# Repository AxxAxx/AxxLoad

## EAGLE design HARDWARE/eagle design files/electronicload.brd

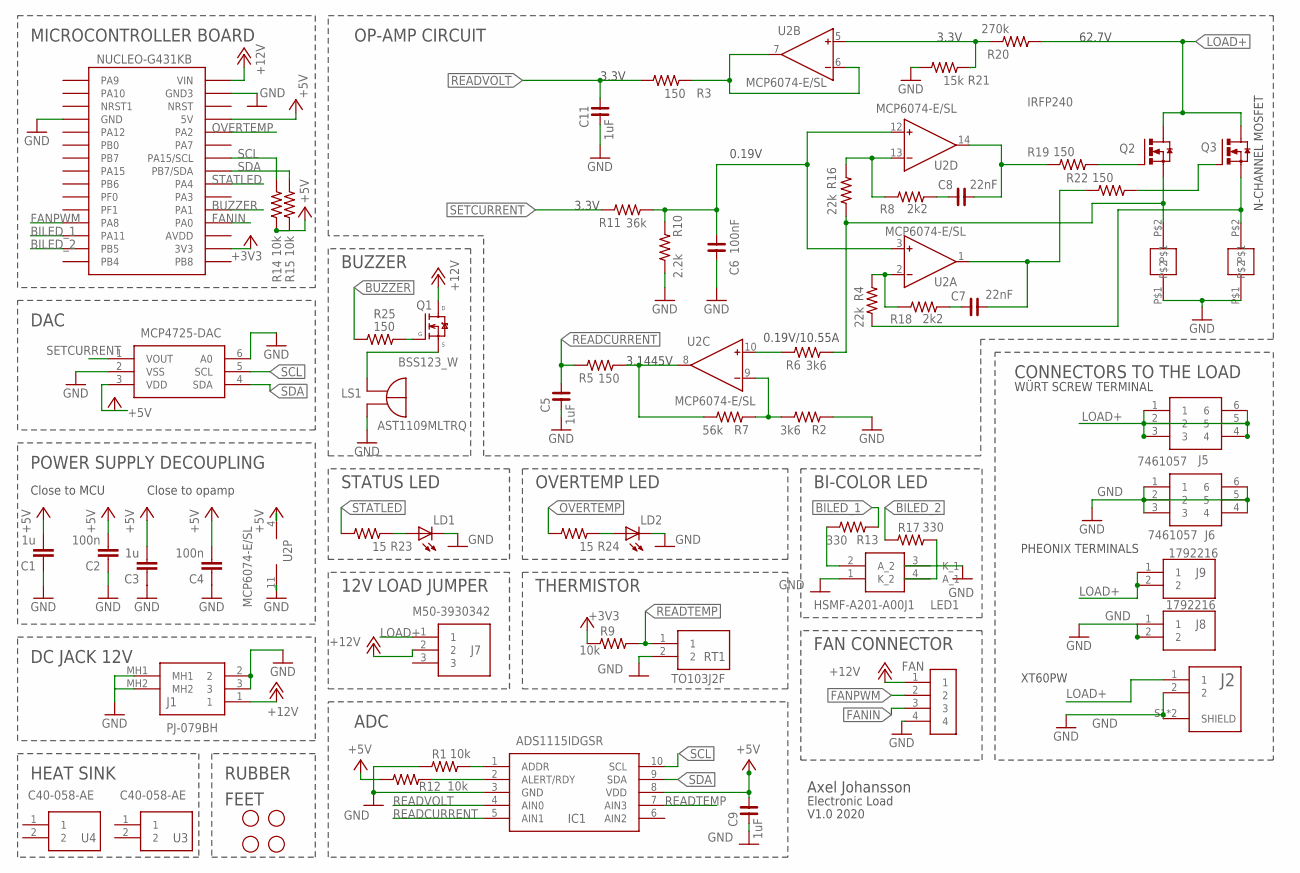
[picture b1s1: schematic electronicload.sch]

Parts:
C1, C3: 1u; C0603K; TOLERANCE 10%; VOLTAGE 16V; DIGIKEY 311-1444-1-ND
C2, C4: 100n; C0603K; TOLERANCE 10%; VOLTAGE 50V; DIGIKEY 445-7456-1-ND
C5, C9, C11: 1uF; C0805
C6: 100nF; C0805
C7, C8: 22nF; C0805
FAN: B4B-PH-K-S(LF)(SN); JST_B4B-PH-K-S(LF)(SN)
IC1: ADS1115IDGSR; SOP50P490X110-10N
J1: PJ-079BH; PJ079BH
J2: XT60PW-F; AMASS_XT60PW-F
J5, J6: 7461057
J7: M50-3930342; M503930342
J8, J9: 1792216
LD1, LD2: LEDCHIP-LED0805; CHIP-LED0805
LED1: HSMF-A201-A00J1; AVAGO_PLCC4
LS1: AST1109MLTRQ; XDCR_AST1109MLTRQ
MCP4725-DAC: MCP4725A0T-E_CH; SOT95P270X145-6N
Q1: BSS123_W; SOT23_GSD_W
Q2, Q3: IRFP240; TO247AC
R1, R9, R12, R14, R15: 10k; R0805
R2, R6: 3k6; R0805
R3, R5, R19, R22, R25: 150; R0805
R4, R16: 22k; R0805
R7: 56k; R0805
R8, R18: 2k2; R0805
R10: 2.2k; R0805
R11: 36k; R0805
R13, R17: 330; R0805
R20: 270k; R0805
R21: 15k; R0805
R23, R24: 15; R0805
RT1: TO103J2F; TO508P483X1016X2337-2P
U2: MCP6074-E/SL; SO14
U3, U4: C40-058-AE; C40058AE
U$1: NANO
U$2, U$5, U$6, U$7: RUBBER_FEET
U$3, U$4: CURRENTSENSE_RESISTOR_SMD2817

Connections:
+3V3: R9.1, U$1.RX1 (3V3)
+5V: C1.2, C2.2, C3.2, C4.2, C9.2, IC1.8 (VDD), MCP4725-DAC.3 (VDD), R12.1, R14.1, R15.1, U2.4 (V+), U$1.D9 (5V)
+12V: FAN.1, J1.1, J7.2, Q1.D, U$1.D12 (VIN)
BILED_1: R13.1, U$1.RST (PA11)
BILED_2: R17.1, U$1.GND (PB5)
BUZZER: R25.1, U$1.D2 (PA1)
FANIN: FAN.3, U$1.GND1 (PA0)
FANPWM: FAN.2, U$1.5V (PA8)
GND: C1.1, C2.1, C3.1, C4.1, C5.1, C6.1, C9.1, C11.1, FAN.4, IC1.3 (GND), J1.2, J1.3, J1.MH1, J1.MH2, J2.2, J2.S1 (SHIELD), J2.S2 (SHIELD), J6.1, J6.2, J6.3, J6.4, J6.5, J6.6, J8.1, J8.2, LD1.C, LD2.C, LED1.1 (K_2), LED1.3 (K_1), LS1.2, MCP4725-DAC.2 (VSS), MCP4725-DAC.6 (A0), R1.1, R2.1, R10.2, R21.2, RT1.2, U2.11 (V-), U$1.A0 (GND), U$1.D11 (GND3), U$3.P$1, U$4.P$1
LOAD+: J2.1, J5.1, J5.2, J5.3, J5.4, J5.5, J5.6, J7.1, J9.1, J9.2, Q2.2 (D), Q3.2 (D), R20.1
unnamed: C8.1, R19.1, U2.14 (OUT)
unnamed: R3.1, U2.6 (IN-), U2.7 (OUT)
unnamed: R6.2, U2.10 (IN+)
unnamed: R8.1, R16.1, U2.13 (IN-)
unnamed: R20.2, R21.1, U2.5 (IN+)
unnamed: Q2.1 (G), R19.2
unnamed: R2.2, R7.1, U2.9 (IN-)
unnamed: IC1.1 (ADDR), R1.2
unnamed: R5.1, R7.2, U2.8 (OUT)
unnamed: IC1.2 (ALERT/RDY), R12.2
unnamed: LED1.4 (A_1), R17.2
unnamed: C8.2, R8.2
unnamed: LED1.2 (A_2), R13.2
unnamed: Q2.3 (S), R6.1, R16.2, U$4.P$2
unnamed: Q3.3 (S), R4.2, U$3.P$2
unnamed: R4.1, R18.1, U2.2 (IN-)
unnamed: C6.2, R10.1, R11.1, U2.3 (IN+), U2.12 (IN+)
unnamed: C7.2, R18.2
unnamed: Q3.1 (G), R22.2
unnamed: C7.1, R22.1, U2.1 (OUT)
unnamed: LD1.A, R23.1
unnamed: LD2.A, R24.1
unnamed: LS1.1, Q1.S
unnamed: Q1.G, R25.2
OVERTEMP: R24.2, U$1.D8 (PA2)
READCURRENT: C5.2, IC1.5 (AIN1), R5.2
READTEMP: IC1.7 (AIN3), R9.2, RT1.1
READVOLT: C11.2, IC1.4 (AIN0), R3.2
SCL: IC1.10 (SCL), MCP4725-DAC.5 (SCL), R14.2, U$1.D6 (PA15/SCL)
SDA: IC1.9 (SDA), MCP4725-DAC.4 (SDA), R15.2, U$1.D5 (PB7/SDA)
SETCURRENT: MCP4725-DAC.1 (VOUT), R11.2
STATLED: R23.2, U$1.D4 (PA4)

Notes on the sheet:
POWER SUPPLY DECOUPLING
PHEONIX TERMINALS
WÜRT SCREW TERMINAL
N-CHANNEL MOSFET
3.3V
62.7V
0.19V
0.19V/10.55A
3.1445V
Electronic Load
V1.0 2020
Close to MCU
Close to opamp
HEAT SINK
CONNECTORS TO THE LOAD
MICROCONTROLLER BOARD
OP-AMP CIRCUIT
Axel Johansson
DAC
RUBBER
FEET
DC JACK 12V
THERMISTOR
ADC
FAN CONNECTOR
XT60PW
BI-COLOR LED
12V LOAD JUMPER
STATUS LED
OVERTEMP LED
BUZZER

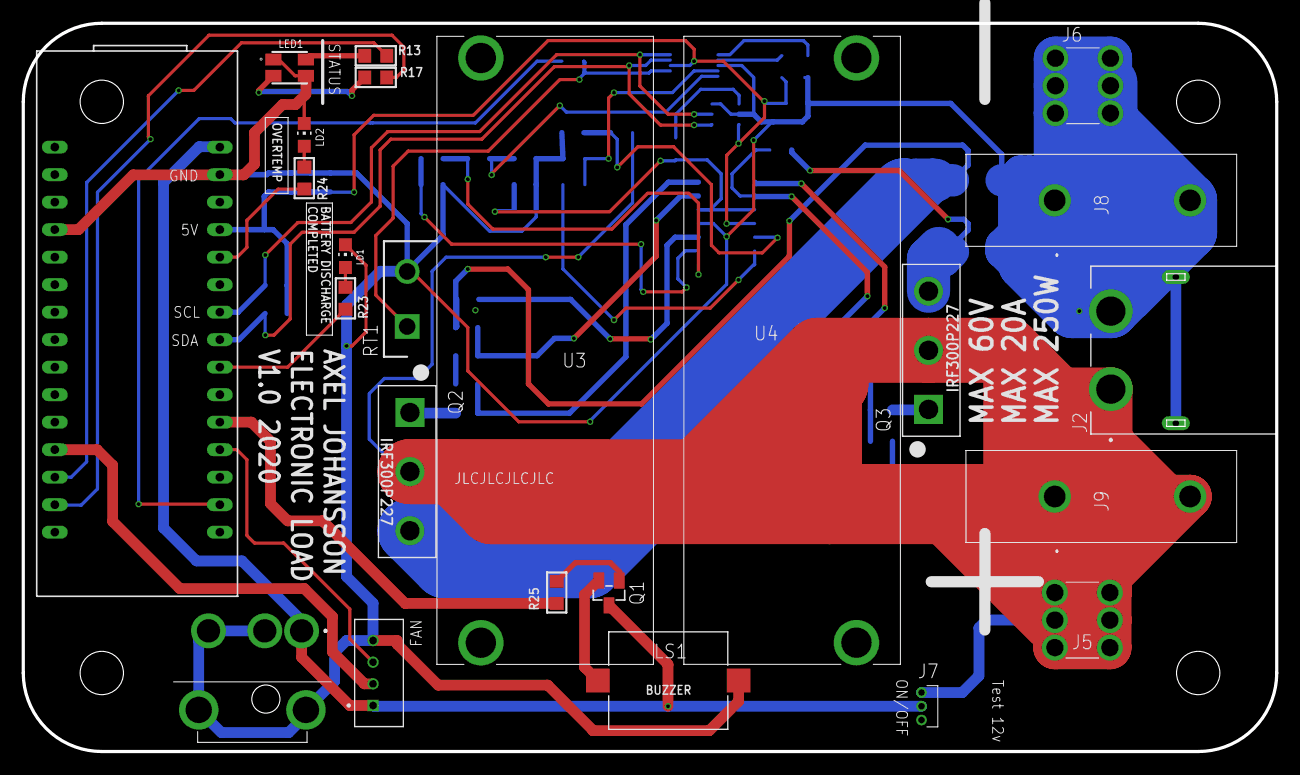
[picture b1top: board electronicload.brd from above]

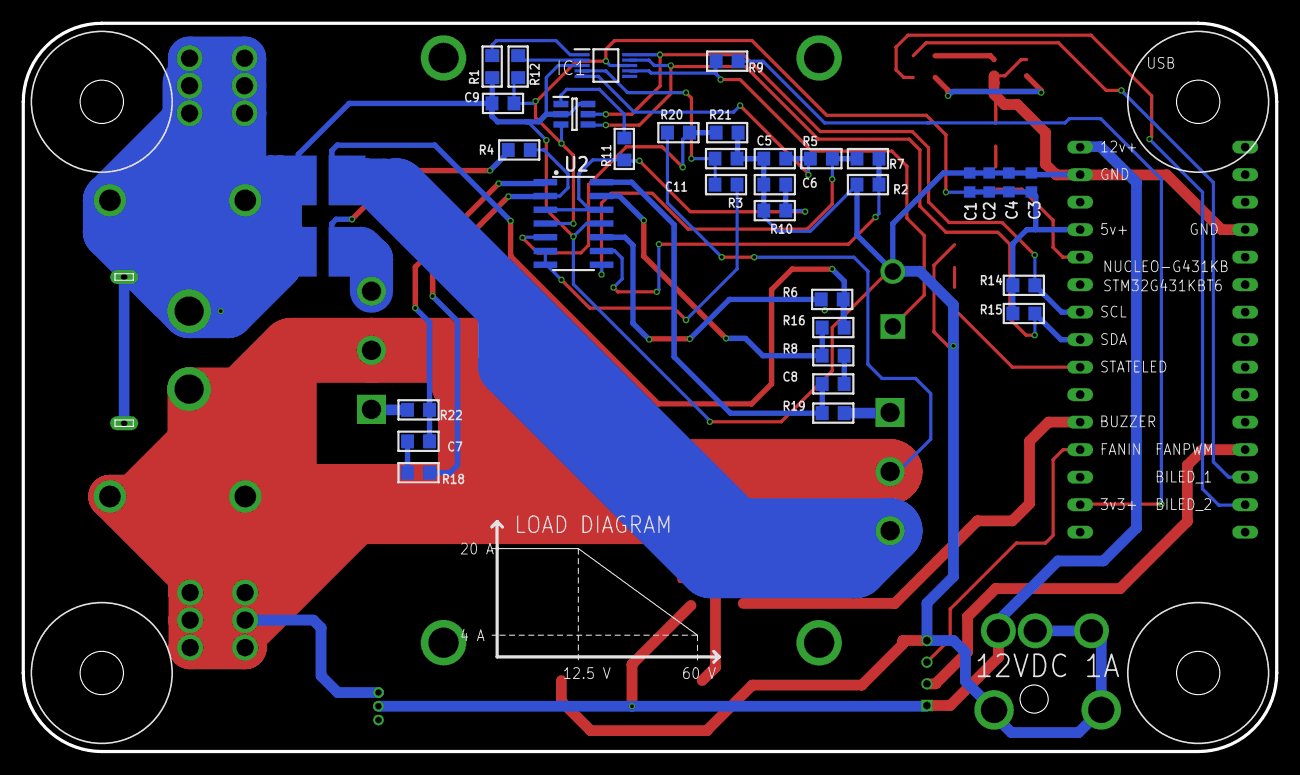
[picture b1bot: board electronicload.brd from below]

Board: 2 copper layers, 115.8 x 67.2 mm, 63 parts (35 on the bottom side), 42 nets.

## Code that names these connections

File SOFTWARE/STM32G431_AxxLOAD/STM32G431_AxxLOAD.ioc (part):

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Mcu.Name=STM32G431K(6-8-B)Tx
Mcu.Package=LQFP32
Mcu.UserName=STM32G431KBTx
PA0.GPIOParameters=GPIO_Label
PA0.GPIO_Label=FANIN
PA0.Signal=GPIO_Input
PA1.GPIOParameters=GPIO_Label
PA1.GPIO_Label=FET1_TEMP
PA1.Mode=IN2-Single-Ended
PA1.Signal=ADC1_IN2
PA10.Mode=Asynchronous
PA10.Signal=USART1_RX
PA11.GPIOParameters=GPIO_Label
PA11.GPIO_Label=BILED_1
PA11.Signal=GPIO_Output
PA12.GPIOParameters=GPIO_Label
PA12.GPIO_Label=DISCHARGE_LED
PA12.Signal=GPIO_Output
PA15.Mode=I2C
PA15.Signal=I2C1_SCL
PA2.Mode=Asynchronous
PA2.Signal=USART2_TX
PA3.Mode=Asynchronous
PA3.Signal=USART2_RX
PA4.GPIOParameters=GPIO_Label
PA4.GPIO_Label=FET2_TEMP
PA4.Mode=IN17-Single-Ended
PA4.Signal=ADC2_IN17
PA7.GPIOParameters=GPIO_Label
PA7.GPIO_Label=PCB_TEMP
PA7.Mode=IN4-Single-Ended
PA7.Signal=ADC2_IN4
PA8.GPIOParameters=GPIO_Label
PA8.GPIO_Label=FAN_PWM
PA8.Signal=S_TIM1_CH1
PA9.Mode=Asynchronous
PA9.Signal=USART1_TX
PB0.GPIOParameters=GPIO_Label
PB0.GPIO_Label=BUZZER
PB0.Signal=S_TIM3_CH3
PB4.GPIOParameters=GPIO_Label
PB4.GPIO_Label=OVERTEMP
PB4.Signal=GPIO_Output
PB5.GPIOParameters=GPIO_Label
PB5.GPIO_Label=BILED_2
PB5.Signal=GPIO_Output
PB7.Mode=I2C
PB7.Signal=I2C1_SDA
PB8-BOOT0.GPIOParameters=GPIO_Label
PB8-BOOT0.GPIO_Label=LED
PB8-BOOT0.Signal=GPIO_Output
PF0-OSC_IN.Mode=HSE-External-Oscillator
PF0-OSC_IN.Signal=RCC_OSC_IN
PF1-OSC_OUT.Mode=HSE-External-Oscillator
PF1-OSC_OUT.Signal=RCC_OSC_OUT
RCC.HSE_VALUE=24000000
RCC.SYSCLKFreq_VALUE=24000000
RCC.SYSCLKSource=RCC_SYSCLKSOURCE_HSE
board=custom

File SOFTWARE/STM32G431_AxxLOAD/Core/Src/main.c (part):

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uint32_t integrationTime = 0;
uint32_t milliAmpHours = 0;
uint32_t milliWattHours = 0;
uint16_t setCurrent = 0;           // interval at which to blink (milliseconds)
float voltageCompensationConstant = 3.57081997924;
float currentCompensationConstant = 1.01125769786;
float temperatureCompensationConstant = 1; //VOLT: 1.98 (16 deg) - 0.065 (152 deg)
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	struct statusValues my_statusValues;        /* Declare Book1 of type Book */
	my_statusValues.amperehours=0;
	my_statusValues.watthours=0;
	my_statusValues.setCurrent=0;
  /* USER CODE END 1 */

  /* MCU Configuration--------------------------------------------------------*/
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
		else if((strncmp(array[0], "stop" ,10) == 0) || strncmp(array[0], "s" ,10) == 0){
			reportStatus = false;
			my_statusValues.setCurrent = 0;
			CW_MODE = false;
			CR_MODE = false;
			PULSE_MODE = false;
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
	  HAL_GPIO_TogglePin(GPIOB, LED_Pin); //Toggle LED
	  //HAL_GPIO_TogglePin(GPIOA,  DISCHARGE_LED_Pin); //Toggle LED
	  //HAL_GPIO_TogglePin(GPIOB,  OVERTEMP_Pin);


	  if(PULSE_MODE){
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			  if (PULSE_TOGGLE){
				  PULSE_TOGGLE = false;
				  my_statusValues.setCurrent = pulseCurrent;
				  HAL_GPIO_TogglePin(GPIOA, BILED_1_Pin); //Toggle LED
			  }
			  else{
				  PULSE_TOGGLE = true;
				  my_statusValues.setCurrent = 0;
				  HAL_GPIO_TogglePin(GPIOA, BILED_2_Pin); //Toggle LED
			  }
			  previousMillis_PULSE = HAL_GetTick();
		  }
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	  }

	  if(my_statusValues.measuredVoltage<minVolt){
			my_statusValues.setCurrent = 0;
			reportStatus = false;
			BEEP(&htim3);
		  	debugPrintln(&huart2, "Min voltage reached. Stopped discharge");
	  }

	  if(my_statusValues.measuredPower/1000>maxWatt){
			my_statusValues.setCurrent = 0;
			reportStatus = false;
			BEEP(&htim3);
			debugPrintln(&huart2, "OVERPOWER, Stopped discharge");
	  }

	  if(my_statusValues.measuredCurrent/1000>maxCurrent){
			my_statusValues.setCurrent = 0;
			reportStatus = false;
			BEEP(&htim3);
			debugPrintln(&huart2, "OVERCURRENT, Stopped discharge");
	  }

	  if((my_statusValues.MOSFET1_Temp>maxTemp*10) || (my_statusValues.MOSFET2_Temp>maxTemp*10)){
			my_statusValues.setCurrent = 0;
			reportStatus = false;
			BEEP(&htim3);
			HAL_Delay(50);
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  __HAL_RCC_GPIOB_CLK_ENABLE();

  /*Configure GPIO pin Output Level */
  HAL_GPIO_WritePin(GPIOA, BILED_1_Pin|DISCHARGE_LED_Pin, GPIO_PIN_RESET);

  /*Configure GPIO pin Output Level */
  HAL_GPIO_WritePin(GPIOB, OVERTEMP_Pin|BILED_2_Pin|LED_Pin, GPIO_PIN_RESET);

  /*Configure GPIO pin : FANIN_Pin */
  GPIO_InitStruct.Pin = FANIN_Pin;
  GPIO_InitStruct.Mode = GPIO_MODE_INPUT;
  GPIO_InitStruct.Pull = GPIO_NOPULL;
  HAL_GPIO_Init(FANIN_GPIO_Port, &GPIO_InitStruct);

  /*Configure GPIO pins : BILED_1_Pin DISCHARGE_LED_Pin */
  GPIO_InitStruct.Pin = BILED_1_Pin|DISCHARGE_LED_Pin;
  GPIO_InitStruct.Mode = GPIO_MODE_OUTPUT_PP;
  GPIO_InitStruct.Pull = GPIO_NOPULL;
  GPIO_InitStruct.Speed = GPIO_SPEED_FREQ_LOW;
  HAL_GPIO_Init(GPIOA, &GPIO_InitStruct);

  /*Configure GPIO pins : OVERTEMP_Pin BILED_2_Pin LED_Pin */
  GPIO_InitStruct.Pin = OVERTEMP_Pin|BILED_2_Pin|LED_Pin;
  GPIO_InitStruct.Mode = GPIO_MODE_OUTPUT_PP;
  GPIO_InitStruct.Pull = GPIO_NOPULL;
  GPIO_InitStruct.Speed = GPIO_SPEED_FREQ_LOW;
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}

/* USER CODE BEGIN 4 */
//HAL_GPIO_WritePin(GPIOA, BILED_1_Pin,GPIO_PIN_SET);               //If pressed Led Switch On
//HAL_GPIO_WritePin(GPIOA, BILED_1_Pin,GPIO_PIN_RESET);          //Else Led Switch Off

//HAL_GPIO_WritePin(GPIOA, STATLED_Pin,GPIO_PIN_SET);               //If pressed Led Switch On
//HAL_GPIO_WritePin(GPIOA, STATLED_Pin,GPIO_PIN_RESET);          //Else Led Switch Off
/* USER CODE END 4 */

/**
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
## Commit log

2021-01-04 various updates
2021-02-03 Added Pulse-MODE
2021-02-03 Added interpolation to fan speed controller
2021-02-04 added fan speed as serial output
2021-02-04 Implemented CR and CP modes
2021-02-04 Cleaned up code
2021-02-17 added command history in GUI
2021-04-08 added stop key
2021-04-08 changed maxPower
2021-04-08 minor update
2021-06-11 fixed bug in temperature reading
2023-09-02 change name of of electronicload.pdf to schematic.pdf

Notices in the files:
SOFTWARE/STM32G431_AxxLOAD/Core/Src/main.c:
© Copyright (c) 2020 STMicroelectronics.
All rights reserved.
This software component is licensed by ST under BSD 3-Clause license,
the "License"; You may not use this file except in compliance with the
License. You may obtain a copy of the License at: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
(C) COPYRIGHT STMicroelectronics *****END OF FILE
parts and their libraries:
rc-master-smd: Copyright (C) 2007, Bob Starr
